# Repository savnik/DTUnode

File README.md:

DTUnodeMCU
==============

A DTU version of NodeMCU using ESP8285 instead of ESP8266. ESP8285 has built-in flash memory which ESP8266 does not. Besides that the ESP8285 is very much the same.
This will be send to PCB production in March 2017 and tested afterwards.

## Features

- ESP8285, 26 MHz resonator
- Built-in flash memory
- Built-in Wi-Fi
- Onboard PCB Antenna
- Reset and flash button
- Input voltage from 1.3v to 6 volts
- Diode protection for battery and USB power supply
- JST battery connector
- Built-in battery voltage measurement
- RGB Led
- RFM95 LoRaWAN module
- HDC1010 High Accuracy humidity sensor
- VEML6030 High Accuracy Ambient Light Sensor
- MAG3110 Three axis digital magnetometer
- DS3231 Real time clock
- BMP280 Digital pressure sensor
- Pin headers for FTDI, I2C, Chip enable and 2 GPIO's

- - - - - -
Author Peter Savnik
Supervisor Ali Ozkil

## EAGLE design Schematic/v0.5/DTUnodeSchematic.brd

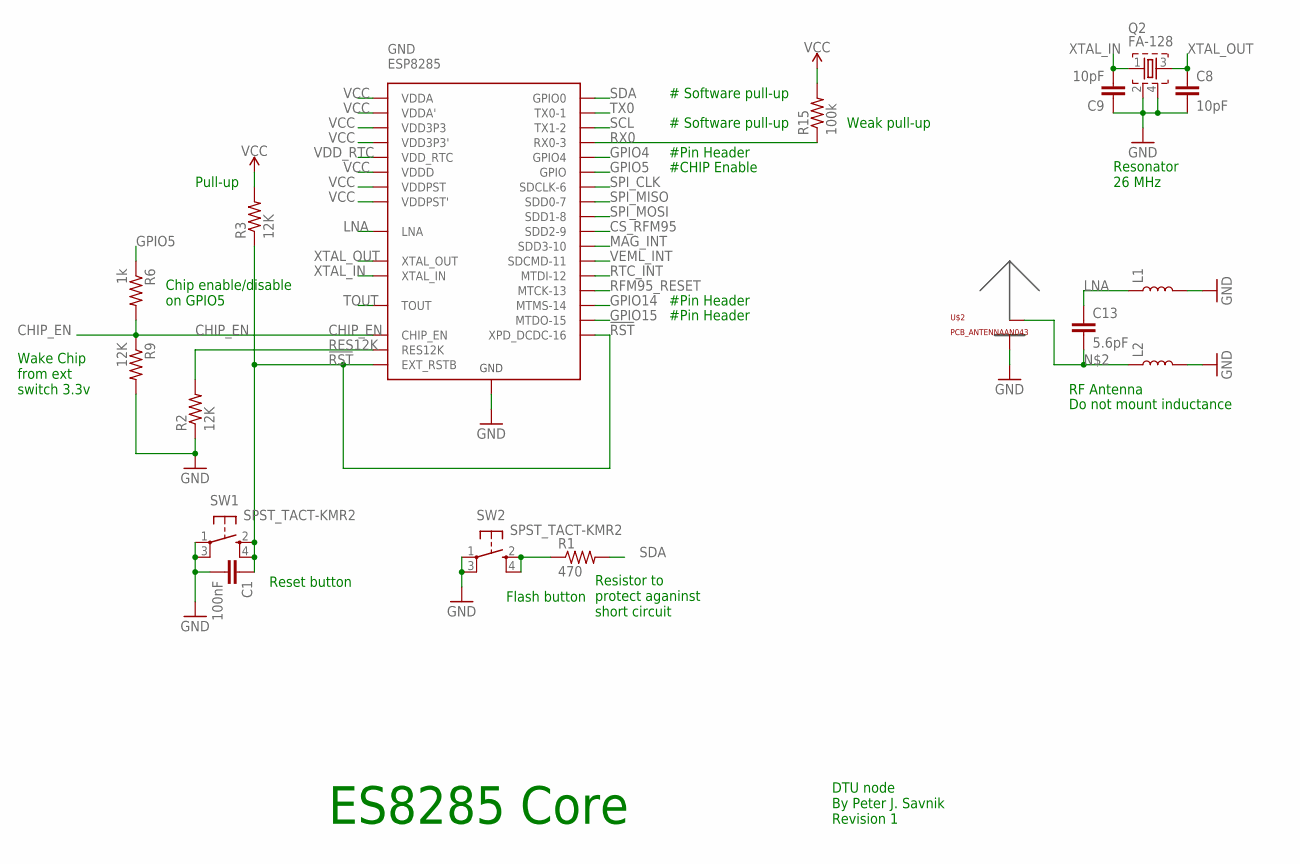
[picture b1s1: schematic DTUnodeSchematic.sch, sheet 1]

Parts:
C1: 100nF; C0402K
C8, C9: 10pF; C0402K
C13: 5.6pF; C0402K
GND: ESP8285; QFN-32
L1, L2: INDUCTOR-0402-3.9NH; 0402
Q2: FA-128
R1: 470; R0402
R2, R3, R9: 12K; R0402
R6: 1k; R0402
R15: 100k; R0402
SW1, SW2: SPST_TACT-KMR2; KMR2
U$2: PCB_ANTENNAAN043; PCB_ANTENNA_TI-AN043

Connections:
!RST: C1.1, GND.P$8 (XPD_DCDC-16), GND.P$32 (EXT_RSTB), R3.1, SW1.2 (S), SW1.4 (S1); also elsewhere on the board
CHIP_EN: GND.P$7 (CHIP_EN), R6.2, R9.1; also elsewhere on the board
CS_RFM95: GND.P$18 (SDD2-9); also elsewhere on the board
GND: C1.2, C8.2, C9.1, GND.33-GND (GND), L1.2, L2.2, Q2.2, Q2.4, R2.1, R9.2, SW1.1, SW1.3 (P1), SW2.1, SW2.3 (P1), U$2.GND; also elsewhere on the board
GPIO4: GND.P$16 (GPIO4); also elsewhere on the board
GPIO5: GND.P$24 (GPIO), R6.1
GPIO14: GND.P$9 (MTMS-14); also elsewhere on the board
GPIO15: GND.P$13 (MTDO-15); also elsewhere on the board
LNA: C13.1, GND.P$2 (LNA), L1.1
MAG_INT: GND.P$19 (SDD3-10); also elsewhere on the board
unnamed: R1.1, SW2.2 (S), SW2.4 (S1)
unnamed: C13.2, L2.1, U$2.ANT (AND)
RES12K: GND.P$31 (RES12K), R2.2
RFM95_RESET: GND.P$12 (MTCK-13); also elsewhere on the board
RTC_INT: GND.P$10 (MTDI-12); also elsewhere on the board
RX0: GND.P$25 (RX0-3), R15.1; also elsewhere on the board
SCL: GND.P$14 (TX1-2); also elsewhere on the board
SDA: GND.P$15 (GPIO0), R1.2; also elsewhere on the board
SPI_CLK: GND.P$21 (SDCLK-6); also elsewhere on the board
SPI_MISO: GND.P$22 (SDD0-7); also elsewhere on the board
SPI_MOSI: GND.P$23 (SDD1-8); also elsewhere on the board
TOUT: GND.P$6 (TOUT); also elsewhere on the board
TX0: GND.P$26 (TX0-1); also elsewhere on the board
VCC: GND.P$1 (VDDA), GND.P$3 (VDD3P3), GND.P$4 (VDD3P3'), GND.P$11 (VDDPST), GND.P$17 (VDDPST'), GND.P$29 (VDDD), GND.P$30 (VDDA'), R3.2, R15.2; also elsewhere on the board
VDD_RTC: GND.P$5 (VDD_RTC)
VEML_INT: GND.P$20 (SDCMD-11); also elsewhere on the board
XTAL_IN: C9.2, GND.P$28 (XTAL_IN), Q2.1
XTAL_OUT: C8.1, GND.P$27 (XTAL_OUT), Q2.3

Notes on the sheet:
Resonator 26 MHz
Chip enable/disable on GPIO5
RF Antenna
Do not mount inductance
DTU node By Peter J. Savnik Revision 1
ES8285 Core
Reset button
Flash button
Resistor to protect aganinst short circuit
#Pin Header
#CHIP Enable
Wake Chip from ext switch 3.3v
# Software pull-up
Weak pull-up
Pull-up

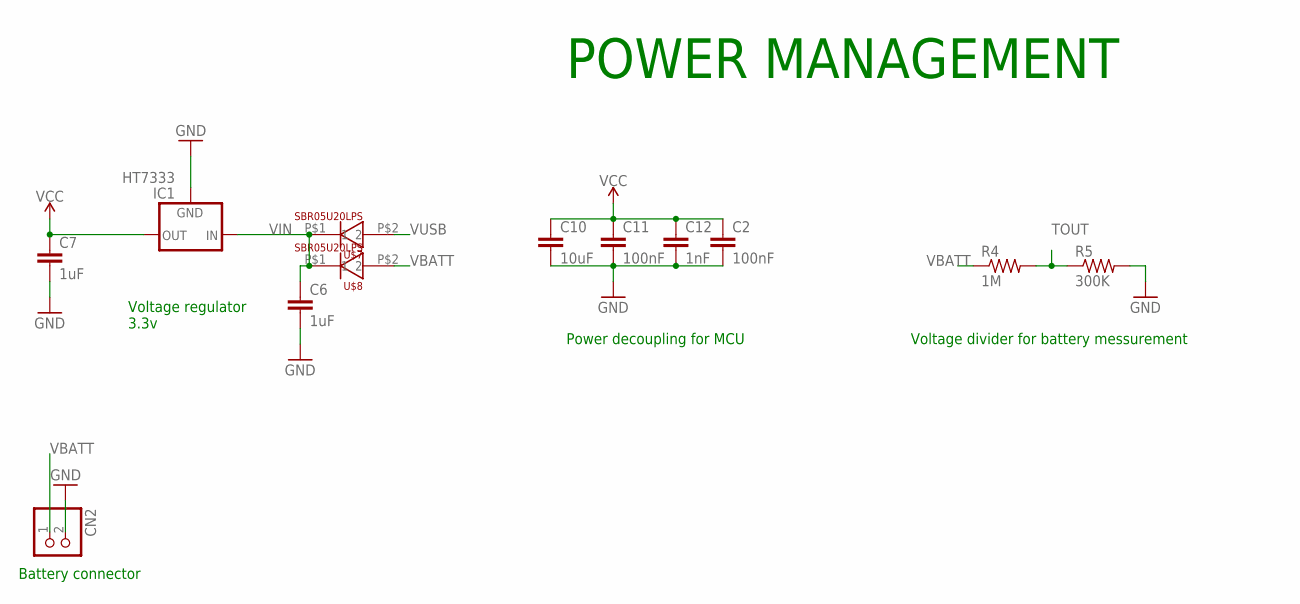
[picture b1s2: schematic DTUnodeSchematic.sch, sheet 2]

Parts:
C2, C11: 100nF; C0402K
C6, C7: 1uF; C0402K
C10: 10uF; C0402K
C12: 1nF; C0402K
CN2: JST_2PIN-THM-RA; JST-PH-2-THM-RA
IC1: HT7333; SOT-89
R4: 1M; R0402
R5: 300K; R0402
U$7, U$8: SBR05U20LPS; X2-DFN1006-2

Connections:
GND: C2.2, C6.2, C7.2, C10.2, C11.2, C12.2, CN2.2 (1), IC1.2 (GND), R5.2; also elsewhere on the board
TOUT: R4.2, R5.1; also elsewhere on the board
VBATT: CN2.1 (2), R4.1, U$8.P$2 (1); also elsewhere on the board
VCC: C2.1, C7.1, C10.1, C11.1, C12.1, IC1.1 (OUT); also elsewhere on the board
VIN: C6.1, IC1.3 (IN), IC1.4 (IN), U$7.P$1 (2), U$8.P$1 (2)
VUSB: U$7.P$2 (1); also elsewhere on the board

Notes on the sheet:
Voltage regulator 3.3v
POWER MANAGEMENT
Battery connector
Power decoupling for MCU
Voltage divider for battery messurement

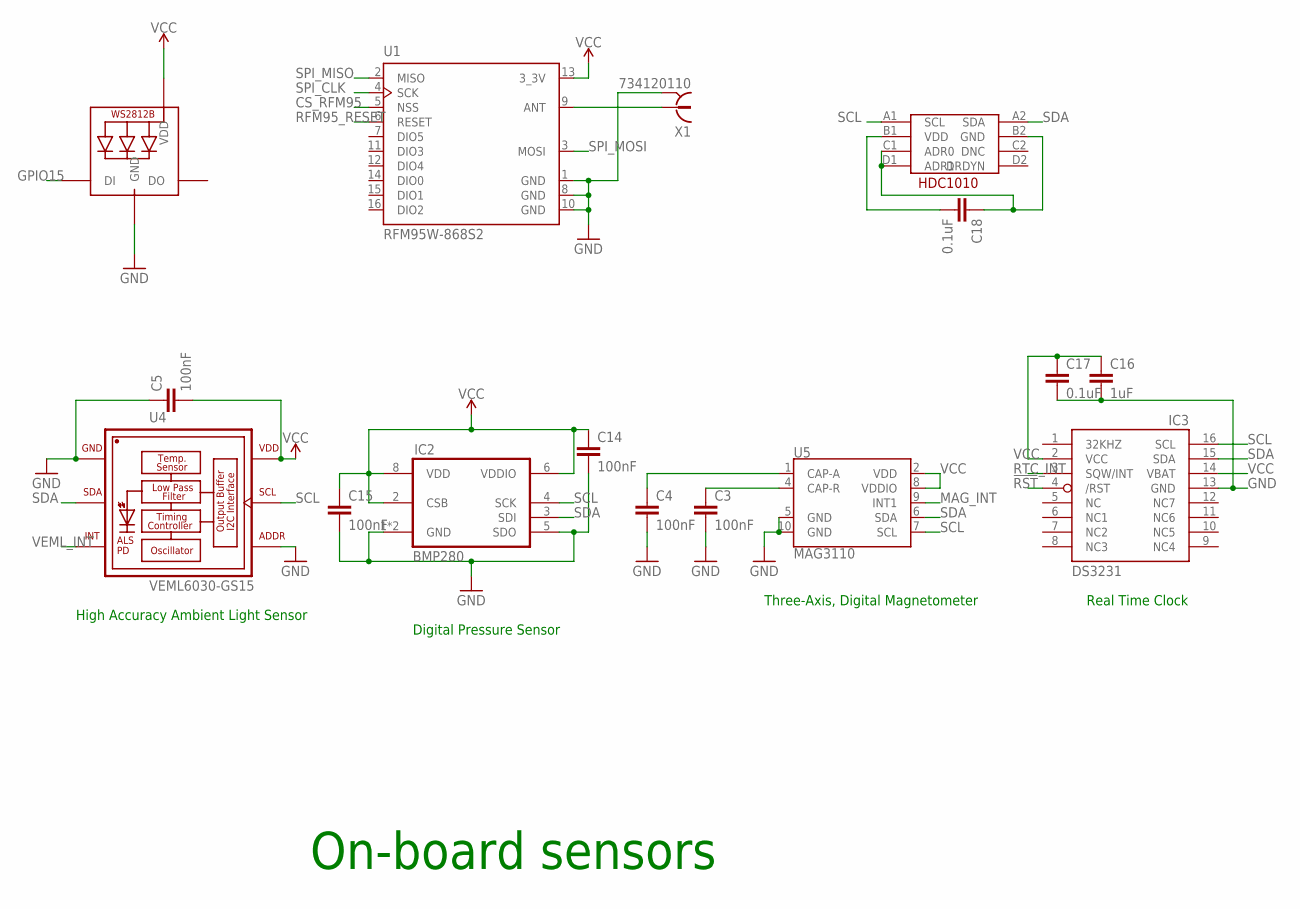
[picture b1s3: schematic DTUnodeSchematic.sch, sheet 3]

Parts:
C3, C4, C5, C14, C15: 100nF; C0402
C16: 1uF; C0402
C17, C18: 0.1uF; C0402
IC2: BMP280
IC3: DS3231/SO; SO16W
LED1: WS2812B5050; WS2812B
U1: RFM95W-868S2; XCVR_RFM95W-868S2
U4: VEML6030-GS15; VISHAY_VEML6030_2X2X0.87
U5: MAG3110; DFN-10
U$3: HDC1010; DSBGA-8
X1: 734120110

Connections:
!RST: IC3.4 (/RST); also elsewhere on the board
CS_RFM95: U1.5 (NSS); also elsewhere on the board
GND: C3.2, C4.2, C5.1, C14.2, C15.2, C16.2, C17.2, IC2.1 (GND), IC2.5 (SDO), IC2.7 (GND), IC3.13 (GND), LED1.3-GND (GND), U1.1 (GND), U1.8 (GND), U1.10 (GND), U4.1 (GND), U4.4 (ADDR), U5.5 (GND), U5.10 (GND), X1.S@1 (2), X1.S@2 (2), X1.S@3 (2); also elsewhere on the board
GPIO15: LED1.4-DIN (DI); also elsewhere on the board
MAG_INT: U5.9 (INT1); also elsewhere on the board
unnamed: U1.9 (ANT), X1.1
unnamed: C18.2, U$3.B1 (VDD)
unnamed: C18.1, U$3.B2 (GND), U$3.C1 (ADR0), U$3.D1 (ADR1)
unnamed: C3.1, U5.4 (CAP-R)
unnamed: C4.1, U5.1 (CAP-A)
RFM95_RESET: U1.6 (RESET); also elsewhere on the board
RTC_INT: IC3.3 (SQW/INT); also elsewhere on the board
SCL: IC2.4 (SCK), IC3.16 (SCL), U4.5 (SCL), U5.7 (SCL), U$3.A1 (SCL); also elsewhere on the board
SDA: IC2.3 (SDI), IC3.15 (SDA), U4.2 (SDA), U5.6 (SDA), U$3.A2 (SDA); also elsewhere on the board
SPI_CLK: U1.4 (SCK); also elsewhere on the board
SPI_MISO: U1.2 (MISO); also elsewhere on the board
SPI_MOSI: U1.3 (MOSI); also elsewhere on the board
VCC: C5.2, C14.1, C15.1, C16.1, C17.1, IC2.2 (CSB), IC2.6 (VDDIO), IC2.8 (VDD), IC3.2 (VCC), IC3.14 (VBAT), LED1.1-VDD (VDD), U1.13 (3_3V), U4.6 (VDD), U5.2 (VDD), U5.8 (VDDIO); also elsewhere on the board
VEML_INT: U4.3 (INT); also elsewhere on the board

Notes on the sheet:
On-board sensors
High Accuracy Ambient Light Sensor
Digital Pressure Sensor
Real Time Clock
Three-Axis, Digital Magnetometer

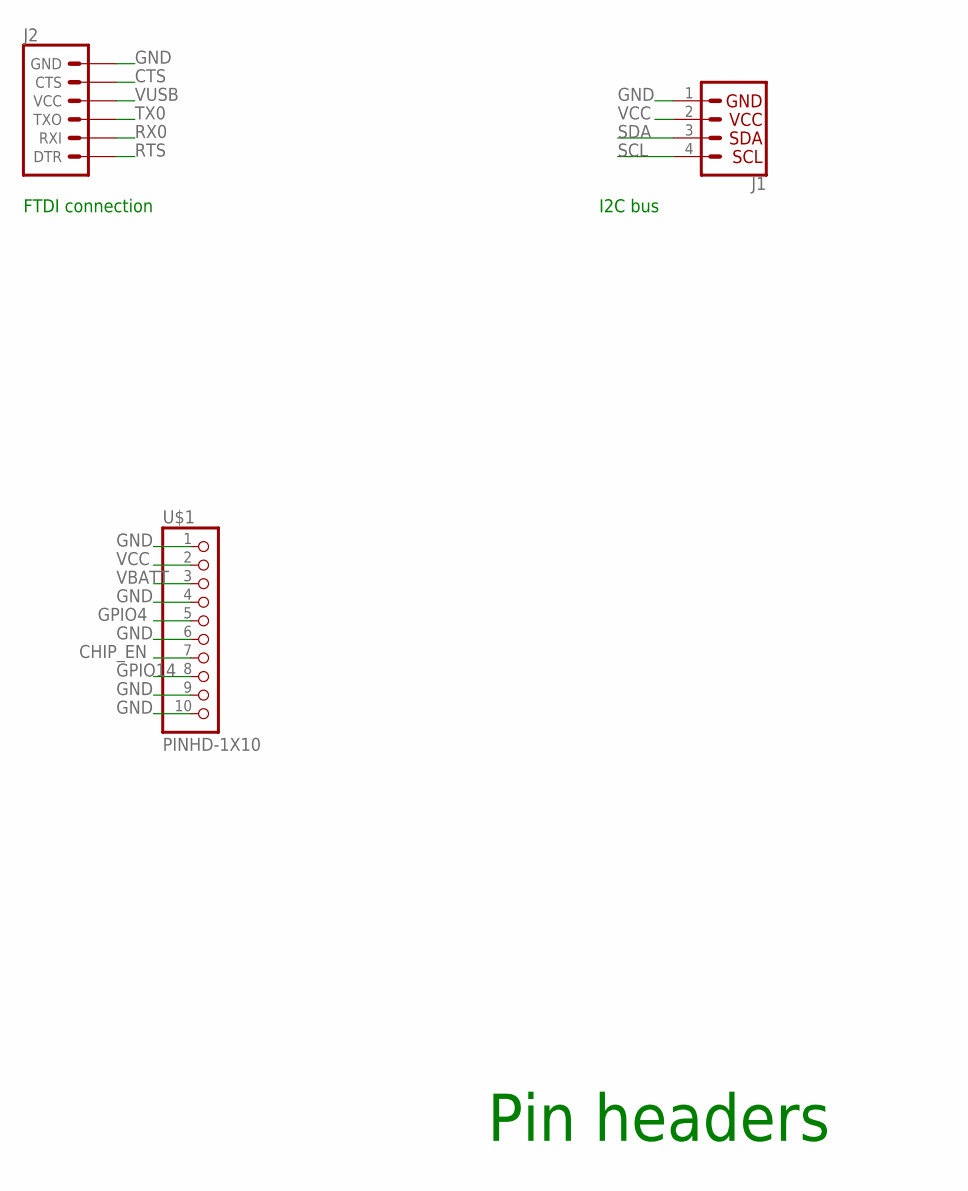
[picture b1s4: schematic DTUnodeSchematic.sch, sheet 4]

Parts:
J1: I2C_STANDARD; 1X04
J2: 6_PIN_SERIAL_TARGET; 1X06
U$1: PINHD-1X10; 1X10-BIG

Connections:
CHIP_EN: U$1.7; also elsewhere on the board
CTS: J2.5 (CTS)
GND: J1.1, J2.6 (GND), U$1.1, U$1.4, U$1.6, U$1.9, U$1.10; also elsewhere on the board
GPIO4: U$1.5; also elsewhere on the board
GPIO14: U$1.8; also elsewhere on the board
RTS: J2.1 (DTR)
RX0: J2.2 (RXI); also elsewhere on the board
SCL: J1.4; also elsewhere on the board
SDA: J1.3; also elsewhere on the board
TX0: J2.3 (TXO); also elsewhere on the board
VBATT: U$1.3; also elsewhere on the board
VCC: J1.2, U$1.2; also elsewhere on the board
VUSB: J2.4 (VCC); also elsewhere on the board

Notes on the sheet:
FTDI connection
Pin headers
I2C bus

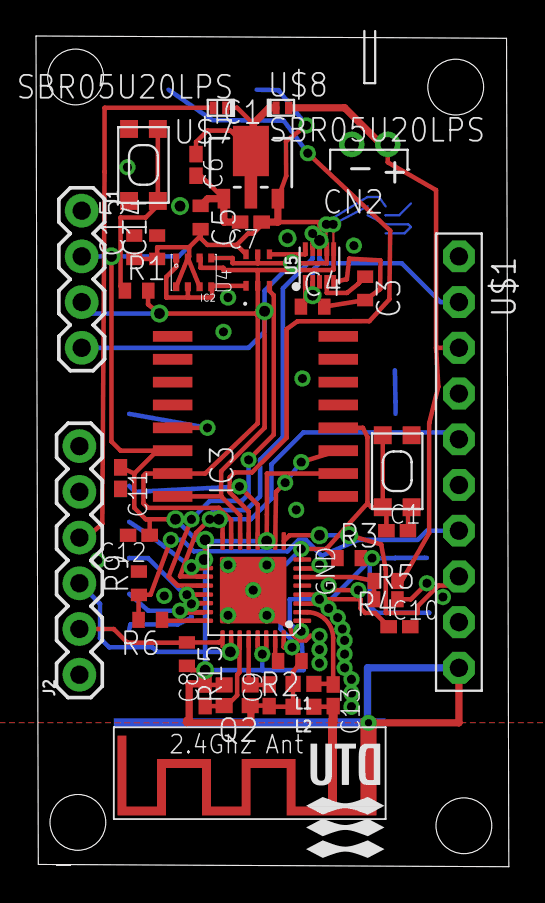
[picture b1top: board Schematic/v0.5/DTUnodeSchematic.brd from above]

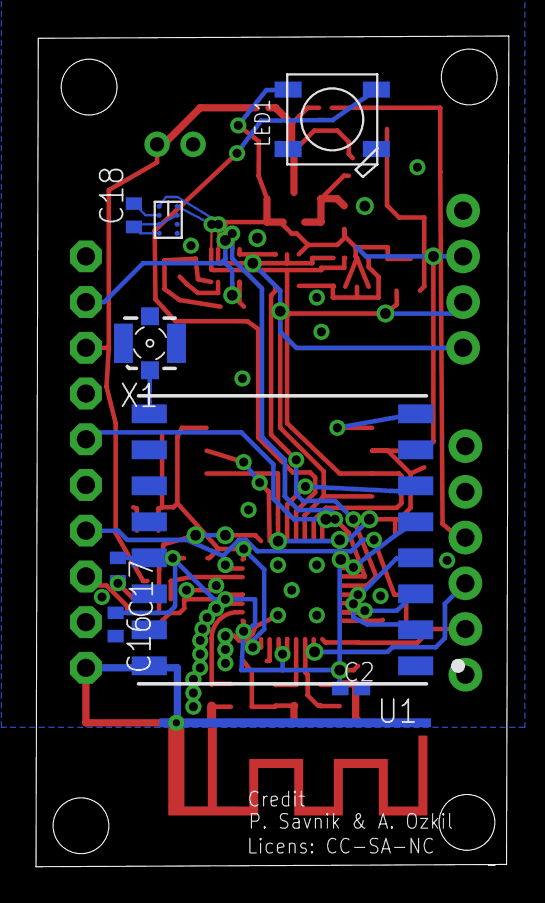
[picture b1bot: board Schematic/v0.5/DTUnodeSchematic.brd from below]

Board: 2 copper layers, 26.3 x 46.2 mm, 48 parts (8 on the bottom side), 35 nets.

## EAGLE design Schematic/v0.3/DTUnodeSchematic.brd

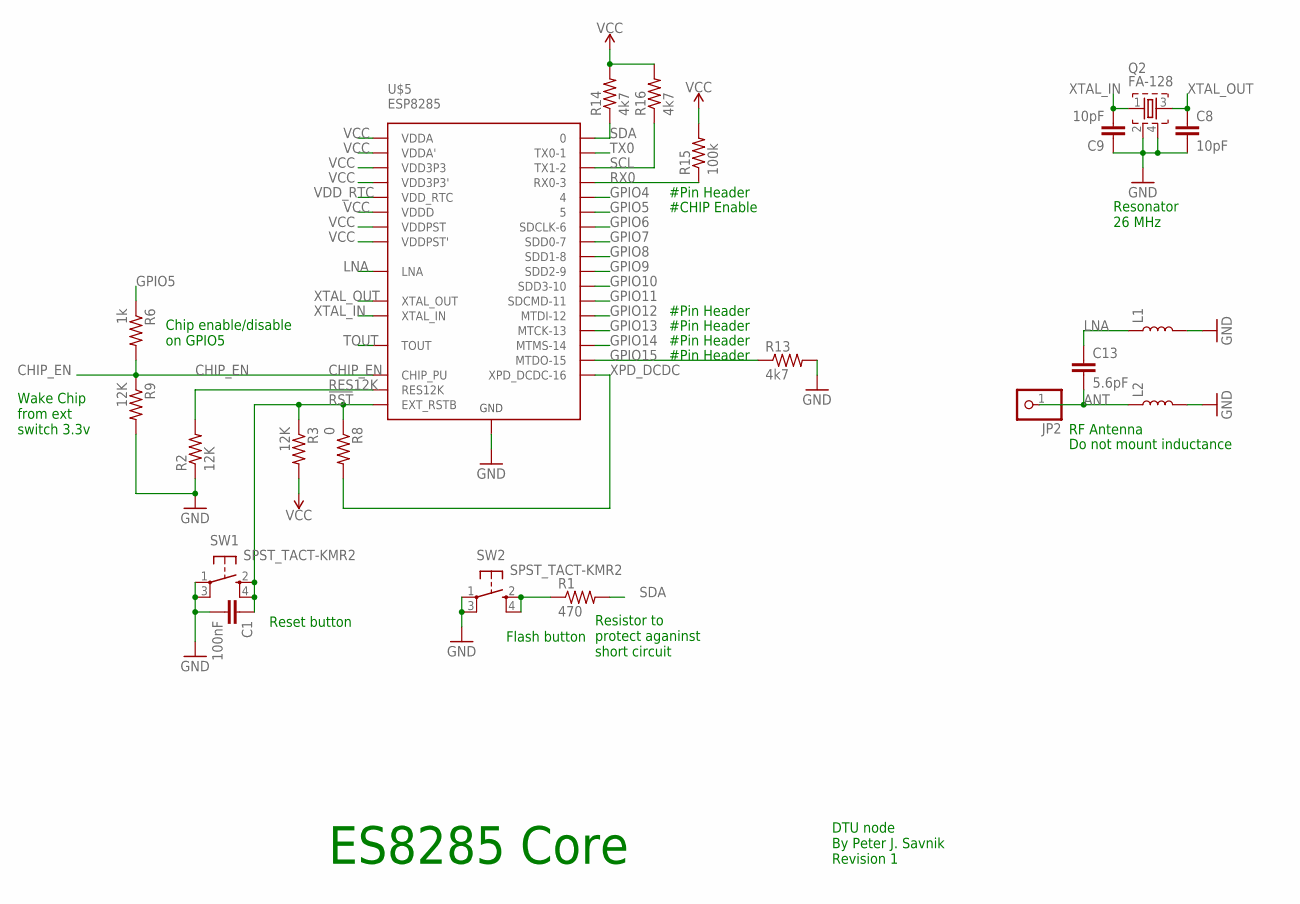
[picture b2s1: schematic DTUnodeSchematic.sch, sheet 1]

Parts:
C1: 100nF; C0402K
C8, C9: 10pF; C0402K
C13: 5.6pF; C0402K
JP2: PINHD-1X1; 1X01
L1, L2: INDUCTOR-0402-3.9NH; 0402
Q2: FA-128
R1: 470; R0402
R2, R3, R9: 12K; R0402
R6: 1k; R0402
R8: 0; R0402
R13, R14, R16: 4k7; R0402
R15: 100k; R0402
SW1, SW2: SPST_TACT-KMR2; KMR2
U$5: ESP8285; QFN-32

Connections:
!RST: C1.1, R3.1, R8.1, SW1.2 (S), SW1.4 (S1), U$5.P$32 (EXT_RSTB)
ANT: C13.2, JP2.1, L2.1
CHIP_EN: R6.2, R9.1, U$5.P$7 (CHIP_PU); also elsewhere on the board
GND: C1.2, C8.2, C9.1, L1.2, L2.2, Q2.2, Q2.4, R2.1, R9.2, R13.2, SW1.1, SW1.3 (P1), SW2.1, SW2.3 (P1), U$5.33-GND (GND); also elsewhere on the board
GPIO4: U$5.P$16 (4); also elsewhere on the board
GPIO5: R6.1, U$5.P$24 (5)
GPIO6: U$5.P$21 (SDCLK-6)
GPIO7: U$5.P$22 (SDD0-7)
GPIO8: U$5.P$23 (SDD1-8)
GPIO9: U$5.P$18 (SDD2-9)
GPIO10: U$5.P$19 (SDD3-10)
GPIO11: U$5.P$20 (SDCMD-11)
GPIO12: U$5.P$10 (MTDI-12); also elsewhere on the board
GPIO13: U$5.P$12 (MTCK-13); also elsewhere on the board
GPIO14: U$5.P$9 (MTMS-14); also elsewhere on the board
GPIO15: R13.1, U$5.P$13 (MTDO-15); also elsewhere on the board
LNA: C13.1, L1.1, U$5.P$2 (LNA)
unnamed: R1.1, SW2.2 (S), SW2.4 (S1)
RES12K: R2.2, U$5.P$31 (RES12K)
RX0: R15.1, U$5.P$25 (RX0-3); also elsewhere on the board
SCL: R16.1, U$5.P$14 (TX1-2); also elsewhere on the board
SDA: R1.2, R14.1, U$5.P$15 (0); also elsewhere on the board
TOUT: U$5.P$6 (TOUT); also elsewhere on the board
TX0: U$5.P$26 (TX0-1); also elsewhere on the board
VCC: R3.2, R14.2, R15.2, R16.2, U$5.P$1 (VDDA), U$5.P$3 (VDD3P3), U$5.P$4 (VDD3P3'), U$5.P$11 (VDDPST), U$5.P$17 (VDDPST'), U$5.P$29 (VDDD), U$5.P$30 (VDDA'); also elsewhere on the board
VDD_RTC: U$5.P$5 (VDD_RTC)
XPD_DCDC: R8.2, U$5.P$8 (XPD_DCDC-16)
XTAL_IN: C9.2, Q2.1, U$5.P$28 (XTAL_IN)
XTAL_OUT: C8.1, Q2.3, U$5.P$27 (XTAL_OUT)

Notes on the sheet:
Resonator 26 MHz
Chip enable/disable on GPIO5
RF Antenna
Do not mount inductance
DTU node By Peter J. Savnik Revision 1
ES8285 Core
Reset button
Flash button
Resistor to protect aganinst short circuit
#Pin Header
#CHIP Enable
Wake Chip from ext switch 3.3v

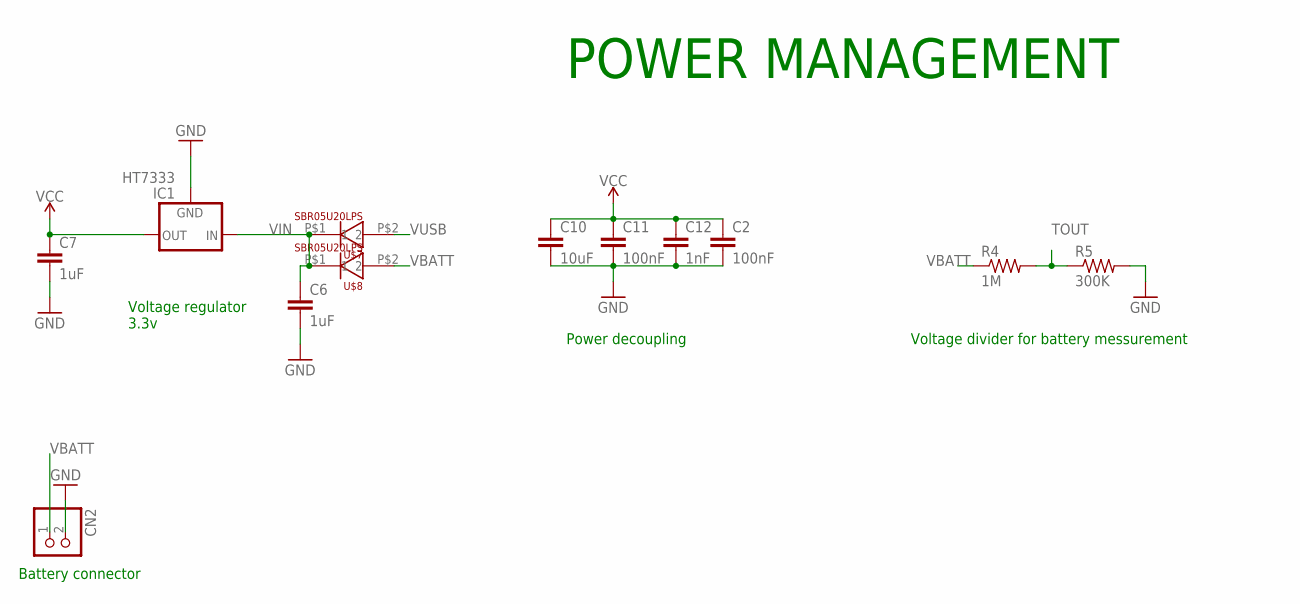
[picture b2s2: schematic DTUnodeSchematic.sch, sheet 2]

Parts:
C2, C11: 100nF; C0402K
C6, C7: 1uF; C0402K
C10: 10uF; C0402K
C12: 1nF; C0402K
CN2: JST_2PIN-THM-RA; JST-PH-2-THM-RA
IC1: HT7333; SOT-89
R4: 1M; R0402
R5: 300K; R0402
U$7, U$8: SBR05U20LPS; X2-DFN1006-2

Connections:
GND: C2.2, C6.2, C7.2, C10.2, C11.2, C12.2, CN2.2 (1), IC1.2 (GND), R5.2; also elsewhere on the board
TOUT: R4.2, R5.1; also elsewhere on the board
VBATT: CN2.1 (2), R4.1, U$8.P$2 (1); also elsewhere on the board
VCC: C2.1, C7.1, C10.1, C11.1, C12.1, IC1.1 (OUT); also elsewhere on the board
VIN: C6.1, IC1.3 (IN), IC1.4 (IN), U$7.P$1 (2), U$8.P$1 (2)
VUSB: U$7.P$2 (1); also elsewhere on the board

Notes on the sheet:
Voltage regulator 3.3v
POWER MANAGEMENT
Battery connector
Power decoupling
Voltage divider for battery messurement

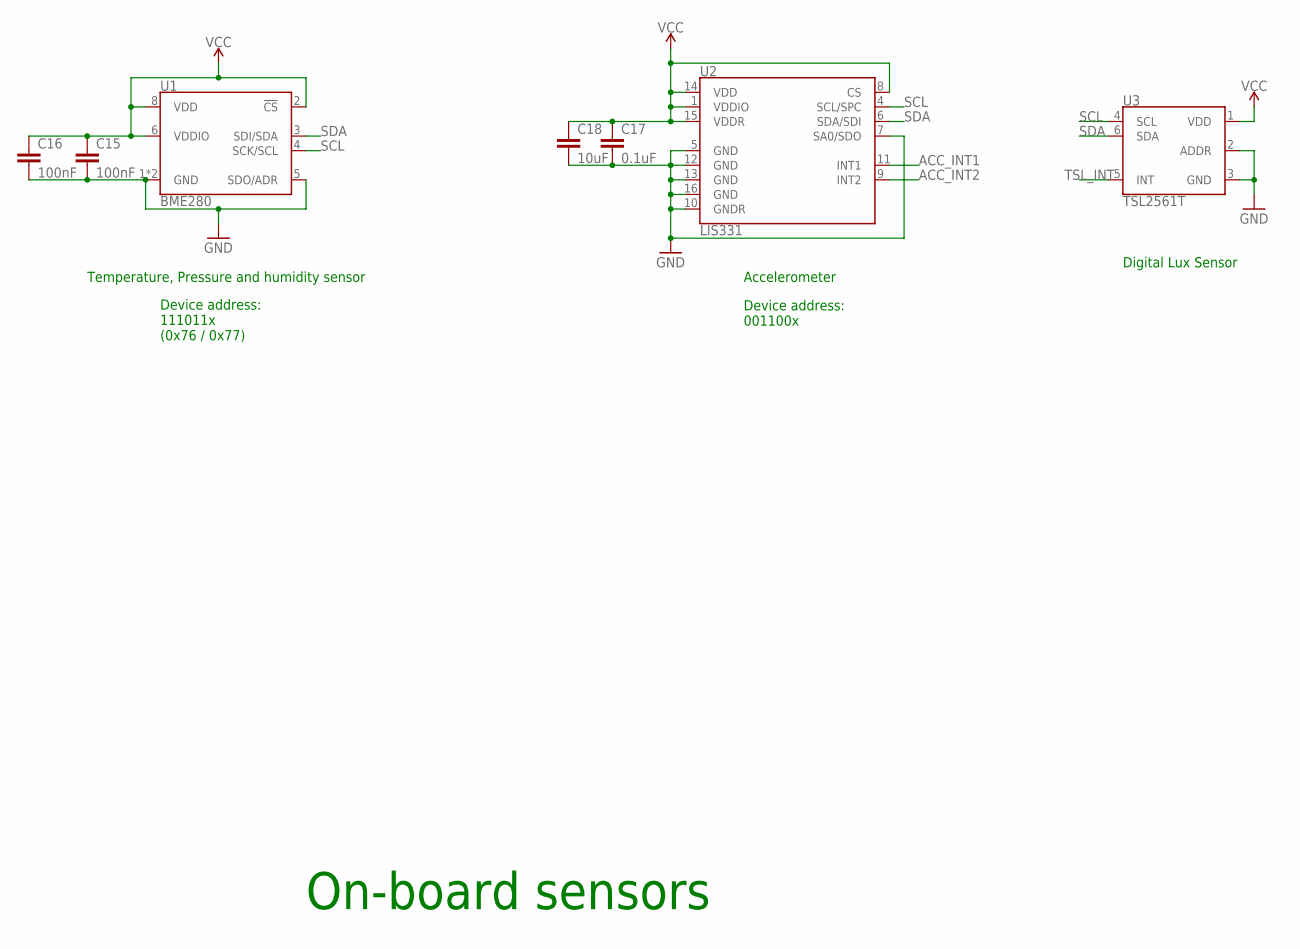
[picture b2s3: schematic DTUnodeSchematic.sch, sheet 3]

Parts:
C15, C16: 100nF; C0402
C17: 0.1uF; C0402
C18: 10uF; C0402
U1: BME280; LGA-8-2.5X2.5
U2: LIS331; LGA-16-3X3
U3: TSL2561T; TMB-6

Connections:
ACC_INT1: U2.11 (INT1)
ACC_INT2: U2.9 (INT2)
GND: C15.2, C16.2, C17.2, C18.2, U1.1 (GND), U1.5 (SDO/ADR), U1.7 (GND), U2.5 (GND), U2.7 (SA0/SDO), U2.10 (GNDR), U2.12 (GND), U2.13 (GND), U2.16 (GND), U3.2 (ADDR), U3.3 (GND); also elsewhere on the board
SCL: U1.4 (SCK/SCL), U2.4 (SCL/SPC), U3.4 (SCL); also elsewhere on the board
SDA: U1.3 (SDI/SDA), U2.6 (SDA/SDI), U3.6 (SDA); also elsewhere on the board
TSL_INT: U3.5 (INT)
VCC: C15.1, C16.1, C17.1, C18.1, U1.2 (!CS), U1.6 (VDDIO), U1.8 (VDD), U2.1 (VDDIO), U2.8 (CS), U2.14 (VDD), U2.15 (VDDR), U3.1 (VDD); also elsewhere on the board

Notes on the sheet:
Temperature, Pressure and humidity sensor
Device address: 111011x (0x76 / 0x77)
Device address: 001100x
Accelerometer
Digital Lux Sensor
On-board sensors

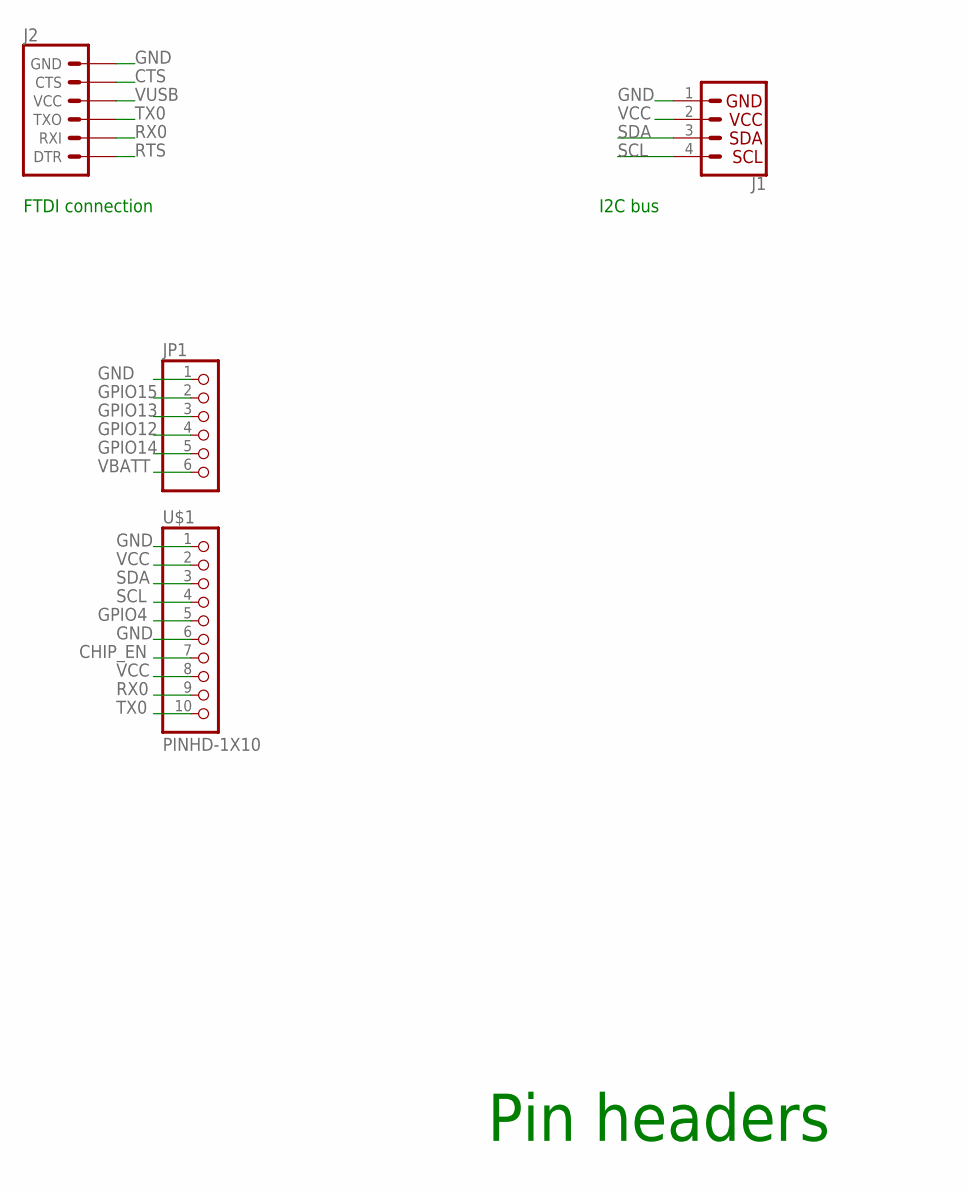
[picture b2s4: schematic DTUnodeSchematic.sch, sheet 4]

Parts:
J1: I2C_STANDARD; 1X04
J2: 6_PIN_SERIAL_TARGET; 1X06
JP1: PINHD-1X6; 1X06
U$1: PINHD-1X10; 1X10-BIG

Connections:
CHIP_EN: U$1.7; also elsewhere on the board
CTS: J2.5 (CTS)
GND: J1.1, J2.6 (GND), JP1.1, U$1.1, U$1.6; also elsewhere on the board
GPIO4: U$1.5; also elsewhere on the board
GPIO12: JP1.4; also elsewhere on the board
GPIO13: JP1.3; also elsewhere on the board
GPIO14: JP1.5; also elsewhere on the board
GPIO15: JP1.2; also elsewhere on the board
RTS: J2.1 (DTR)
RX0: J2.2 (RXI), U$1.9; also elsewhere on the board
SCL: J1.4, U$1.4; also elsewhere on the board
SDA: J1.3, U$1.3; also elsewhere on the board
TX0: J2.3 (TXO), U$1.10; also elsewhere on the board
VBATT: JP1.6; also elsewhere on the board
VCC: J1.2, U$1.2, U$1.8; also elsewhere on the board
VUSB: J2.4 (VCC); also elsewhere on the board

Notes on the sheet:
FTDI connection
Pin headers
I2C bus

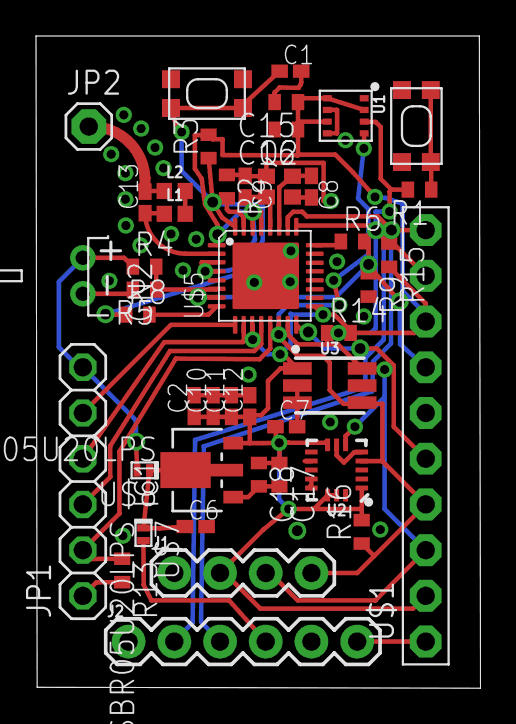
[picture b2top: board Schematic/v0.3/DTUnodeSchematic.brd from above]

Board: 2 copper layers, 24.7 x 36.2 mm, 44 parts (0 on the bottom side), 25 nets.

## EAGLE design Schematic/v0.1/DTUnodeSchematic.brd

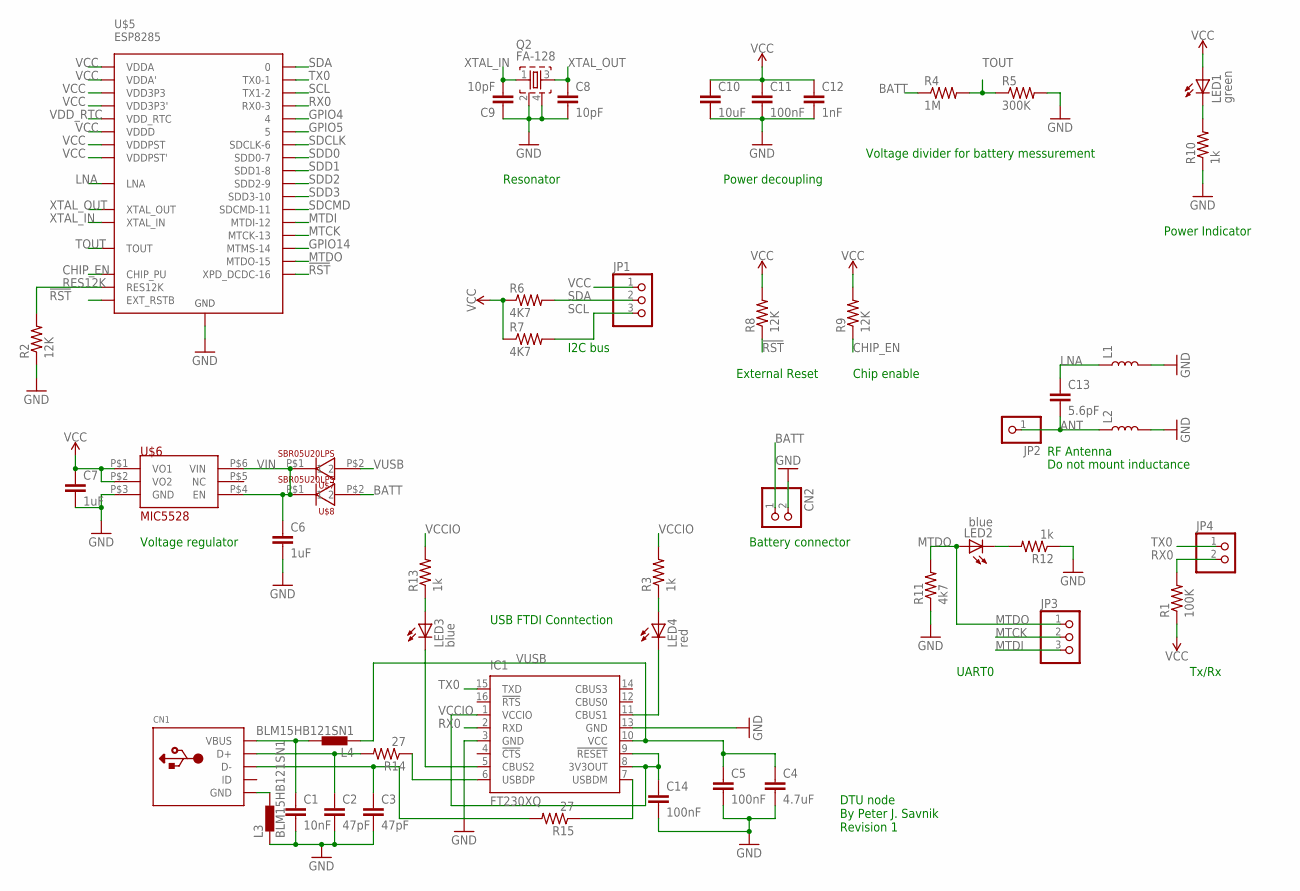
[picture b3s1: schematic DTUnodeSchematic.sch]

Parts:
C1: 10nF; C0402K; MPN MC1206B103K102CT
C2, C3: 47pF; C0402K
C4: 4.7uF; C0402K
C5, C11, C14: 100nF; C0402K
C6, C7: 1uF; C0402K
C8, C9: 10pF; C0402K
C10: 10uF; C0402K
C12: 1nF; C0402K
C13: 5.6pF; C0402K
CN1: USBMINIB; USB-MINIB
CN2: JST_2PIN-THM-RA; JST-PH-2-THM-RA
IC1: FT230XQ; QFN16
JP1, JP3: PINHD-1X3; 1X03
JP2: PINHD-1X1; 1X01
JP4: PINHD-1X2; 1X02
L1, L2: INDUCTOR-0402-3.9NH; 0402
L3, L4: BLM15HB121SN1; 0402
LED1: green; CHIP-LED0603
LED2, LED3: blue; CHIP-LED0603
LED4: red; CHIP-LED0603
Q2: FA-128
R1: 100K; R0402
R2, R8, R9: 12K; R0402
R3, R10, R12, R13: 1k; R0402
R4: 1M; R0402
R5: 300K; R0402
R6, R7: 4K7; R0402
R11: 4k7; R0402
R14, R15: 27; R0402
U$5: ESP8285; QFN-32
U$6: MIC5528; 6-PIN_1.2MMX1.2MM_THIN_FDN(MT)
U$7, U$8: SBR05U20LPS; X2-DFN1006-2

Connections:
!RST: R8.1, U$5.P$8 (XPD_DCDC-16), U$5.P$32 (EXT_RSTB)
ANT: C13.2, JP2.1, L2.1
BATT: CN2.1 (2), R4.1, U$8.P$2 (1)
CHIP_EN: R9.1, U$5.P$7 (CHIP_PU)
GND: C1.2, C2.2, C3.2, C4.2, C5.2, C6.2, C7.2, C8.2, C9.1, C10.2, C11.2, C12.2, C14.2, CN2.2 (1), IC1.3 (GND), IC1.13 (GND), L1.2, L2.2, L3.1, Q2.2, Q2.4, R2.1, R5.2, R10.1, R11.1, R12.1, U$5.33-GND (GND), U$6.P$3 (GND)
GPIO4: U$5.P$16 (4)
GPIO5: U$5.P$24 (5)
GPIO14: U$5.P$9 (MTMS-14)
LNA: C13.1, L1.1, U$5.P$2 (LNA)
MTCK: JP3.2, U$5.P$12 (MTCK-13)
MTDI: JP3.3, U$5.P$10 (MTDI-12)
MTDO: JP3.1, LED2.A, R11.2, U$5.P$13 (MTDO-15)
unnamed: CN1.GND, L3.2
unnamed: IC1.6 (USBDP), R14.1
unnamed: C1.1, CN1.VBUS, L4.2
unnamed: C2.1, CN1.D+, R14.2
unnamed: LED1.C, R10.2
unnamed: C3.1, CN1.D-, R15.2
unnamed: LED2.C, R12.2
unnamed: IC1.7 (USBDM), R15.1
unnamed: LED3.A, R13.1
unnamed: LED4.A, R3.1
unnamed: IC1.5 (CBUS2), LED3.C
unnamed: IC1.11 (CBUS1), LED4.C
RES12K: R2.2, U$5.P$31 (RES12K)
RX0: IC1.2 (RXD), JP4.2, R1.2, U$5.P$25 (RX0-3)
SCL: JP1.3, R7.2, U$5.P$14 (TX1-2)
SDA: JP1.2, R6.2, U$5.P$15 (0)
SDCLK: U$5.P$21 (SDCLK-6)
SDCMD: U$5.P$20 (SDCMD-11)
SDD0: U$5.P$22 (SDD0-7)
SDD1: U$5.P$23 (SDD1-8)
SDD2: U$5.P$18 (SDD2-9)
SDD3: U$5.P$19 (SDD3-10)
TOUT: R4.2, R5.1, U$5.P$6 (TOUT)
TX0: IC1.15 (TXD), JP4.1, U$5.P$26 (TX0-1)
VCC: C7.1, C10.1, C11.1, C12.1, JP1.1, LED1.A, R1.1, R6.1, R7.1, R8.2, R9.2, U$5.P$1 (VDDA), U$5.P$3 (VDD3P3), U$5.P$4 (VDD3P3'), U$5.P$11 (VDDPST), U$5.P$17 (VDDPST'), U$5.P$29 (VDDD), U$5.P$30 (VDDA'), U$6.P$1 (VO1), U$6.P$2 (VO2)
VCCIO: C14.1, IC1.1 (VCCIO), IC1.8 (3V3OUT), IC1.9 (!RESET), R3.2, R13.2
VDD_RTC: U$5.P$5 (VDD_RTC)
VIN: C6.1, U$6.P$4 (EN), U$6.P$6 (VIN), U$7.P$1 (2), U$8.P$1 (2)
VUSB: C4.1, C5.1, IC1.10 (VCC), L4.1, U$7.P$2 (1)
XTAL_IN: C9.2, Q2.1, U$5.P$28 (XTAL_IN)
XTAL_OUT: C8.1, Q2.3, U$5.P$27 (XTAL_OUT)

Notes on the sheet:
Battery connector
Voltage regulator
Resonator
Power decoupling
Voltage divider for battery messurement
I2C bus
External Reset
Chip enable
Power Indicator
RF Antenna
Do not mount inductance
UART0
Tx/Rx
DTU node By Peter J. Savnik Revision 1
USB FTDI Conntection

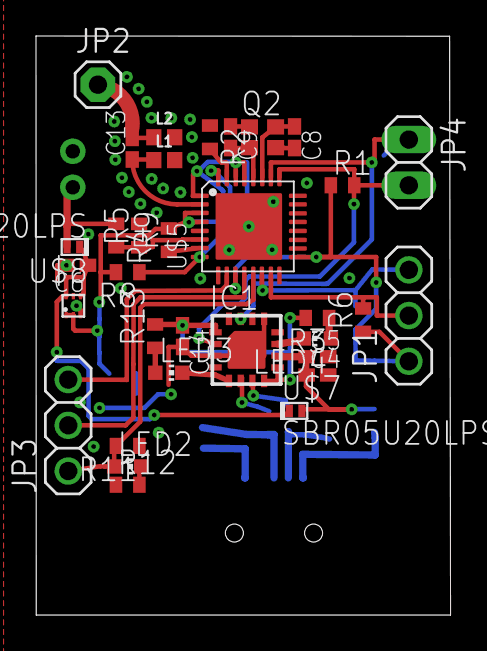
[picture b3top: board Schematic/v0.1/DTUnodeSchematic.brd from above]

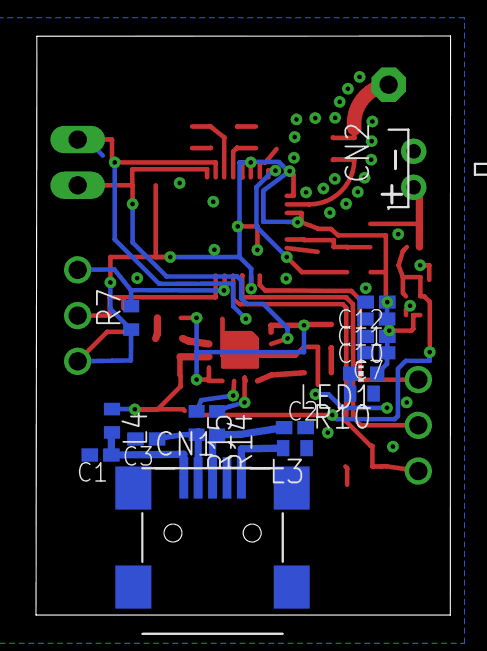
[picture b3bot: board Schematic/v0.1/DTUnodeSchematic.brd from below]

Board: 2 copper layers, 23.0 x 32.2 mm, 49 parts (16 on the bottom side), 33 nets.

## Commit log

2017-02-09 Version 0.1
    Basic Sketch. Needs improvements on:
    low leakage Ldo/boost such as ht7333
    Remove the USB serial chip - it uses too much current. headers for Rx
    tx gnd 3.3v instead.
    Remove the power led - it will kill the battery.
    Some onboard sensors / at least footprint for those : bme280, an
2017-02-12 v0.2 added sensors
2017-02-14 Version 0.3 ESP8285 with flash + boot button, BME280 sensor, LIS331, TLS251T
    next version:
    tilføj: FTDI pins, lora module rfm95, bmp280, hdc1010
2017-02-14 v0.3
2017-02-20 Dev of v. 0.5 start
2017-02-21 v0.5
    Decoupling caps for all components, LED 5050 1655, HDC1010, Silkscreen
    logo, M3 mount holes.
2017-02-21 v0.6
    Reduced vias to 0.3mm
    Found a short circuit
    0.5mm hole for ext antenna (Lora)
2017-02-24 Updateded readme
2017-02-24 changelog

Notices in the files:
parts and their libraries:
SparkFun-Coils: Licensing: Creative Commons ShareAlike 4.0 International - https://creativecommons.org/licenses/by-sa/4.0
